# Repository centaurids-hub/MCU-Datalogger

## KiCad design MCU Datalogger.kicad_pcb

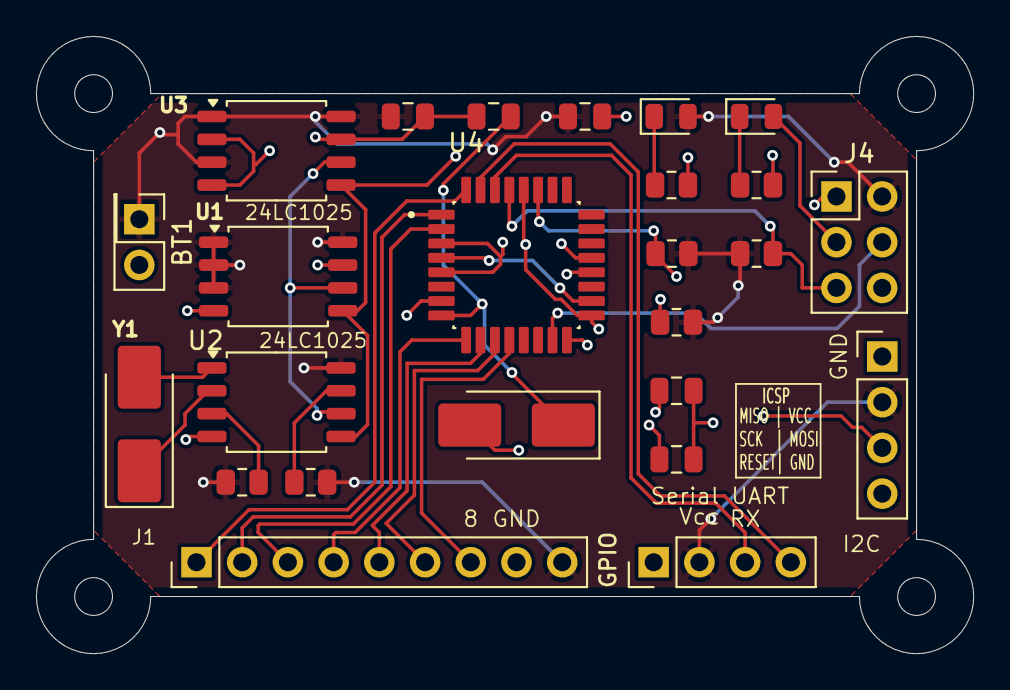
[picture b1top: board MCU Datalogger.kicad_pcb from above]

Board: 4 copper layers, 52.1 x 34.3 mm, 29 parts (0 on the bottom side), 26 nets.

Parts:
BT1: Battery; PinHeader_2x01_P2.54mm_Vertical
C1, C4: 0.1uF; C_0805_2012Metric
C2, C3: 22pF; C_0805_2012Metric
C5: 100nF; C_0805_2012Metric
D1, D2: LED; LED_0805_2012Metric
H1, H2, H3, H4: MountingHole; MountingHole_2.1mm
J1: Conn_01x09_Pin; PinHeader_1x09_P2.54mm_Vertical
J2, J3: Conn_01x04_Pin; PinHeader_1x04_P2.54mm_Vertical
J4: Conn_02x03_Odd_Even; PinHeader_2x03_P2.54mm_Vertical
R1, R2, R6: 10K; R_0805_2012Metric
R3, R4: 4.7K; R_0805_2012Metric
R5, R7: 330; R_0805_2012Metric
U1, U3: 24LC1025; SOIC-8_5.3x5.3mm_P1.27mm
U2: DS1337S_; SOIC-8_5.3x5.3mm_P1.27mm
U4: ATMEGA328P-AU; ATMEGA
Y1: 32.768 KHz; Crystal_SMD_5032-2Pin_5.0x3.2mm_HandSoldering
Y2: 16MHz; Crystal_SMD_5032-2Pin_5.0x3.2mm_HandSoldering

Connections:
/D2: J1.1, U4.32 (PD2)
/D3: J1.2, U4.1 (PD3)
/D4: J1.3, U4.2 (PD4)
/D5: J1.4, U4.9 (PD5)
/D6: J1.5, U4.10 (PD6)
/D7: J1.6, U4.11 (PD7)
/D8: J1.7, U4.12 (PB0)
/MISO: J4.1, U4.16 (PB4)
/MOSI: J4.4, U4.15 (PB3)
/RESET: J4.5, R6.2, U4.29 (PC6/~RESET)
/RX: J3.3, U4.30 (PD0)
/SCL: D1.2 (A), J2.4, J4.3, R3.2, U1.6 (SCL), U2.6 (SCL), U3.6 (SCL), U4.17 (PB5), U4.28 (PC5)
/SDA: J2.3, R4.2, U1.5 (SDA), U2.5 (SDA), U3.5 (SDA), U4.27 (PC4)
/TX: J3.4, U4.31 (PD1)
/Vcc: BT1.1 (+), C1.1, C5.1, D2.2 (A), J1.9, J2.2, J3.2, J4.2, R1.1, R2.1, R3.1, R4.1, R6.1, U1.1 (A0), U1.2 (A1), U1.3 (A2), U1.8 (VCC), U2.8 (VCC), U3.1 (A0), U3.3 (A2), U3.8 (VCC)
GND: BT1.2 (-), C1.2, C2.2, C3.2, C4.1, C5.2, J1.8, J2.1, J3.1, J4.6, R5.1, R7.2, U1.4 (GND), U1.7 (WP), U2.4 (GND), U3.2 (A1), U3.4 (GND), U3.7 (WP), U4.3 (GND), U4.5 (GND), U4.21 (GND)
unnamed: U4.4 (VCC), U4.18 (AVCC)
unnamed: D1.1 (K), R5.2
unnamed: D2.1 (K), R7.1
unnamed: R2.2, U2.7 (SQW/~INT)
unnamed: U2.1 (X1), Y1.2
unnamed: U2.2 (X2), Y1.1
unnamed: R1.2, U2.3 (~INTA)
unnamed: C4.2, U4.20 (AREF)
unnamed: C2.1, U4.7 (PB6), Y2.2
unnamed: C3.1, U4.8 (PB7), Y2.1

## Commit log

2025-09-28 Setup of EEschema for new project
2025-09-28 Have added required symbols to the schematic sheets.
2025-09-28 Changes location of symbols (arrange).
2025-09-28 Completed wiring of main sheet.
2025-09-28 Completed wiring main sheet.
2025-09-28 Allocated GND and Vcc nets to the Power net class.
2025-09-28 Completed comments.
2025-09-28 Completed putting footprints in the library.
2025-09-28 Completed footprints.
2025-09-28 Completed footprints assignments.
2025-09-28 Footprint assignment completed.
2025-09-28 Footprints Fixed
2025-09-28 Footprints were added and fixed.
2025-09-28 Completed placement of footprints.
2025-09-28 Refined and completed outline
2025-09-29 Updated the PCB.
2025-09-29 Changes in Files.
2025-09-29 Completed wirings.
2025-09-29 Completed copper zones.
2025-09-29 PCB copper zones completed.
2025-09-29 Refined routing completed.
2025-09-29 Completed text references and value.
2025-09-29 Symnols added.
2025-09-29 Completed 2 layer.
2025-09-29 2 layer done.
2025-09-29 Completed 2-layer PCB.
2025-09-30 Schec Missing.
2025-09-30 git attributes is added.
2025-09-30 made small change to schenatic.
2025-09-30 Fixed two defects in the schematic.
2025-10-07 Add files via upload
    MCU Datalogger
